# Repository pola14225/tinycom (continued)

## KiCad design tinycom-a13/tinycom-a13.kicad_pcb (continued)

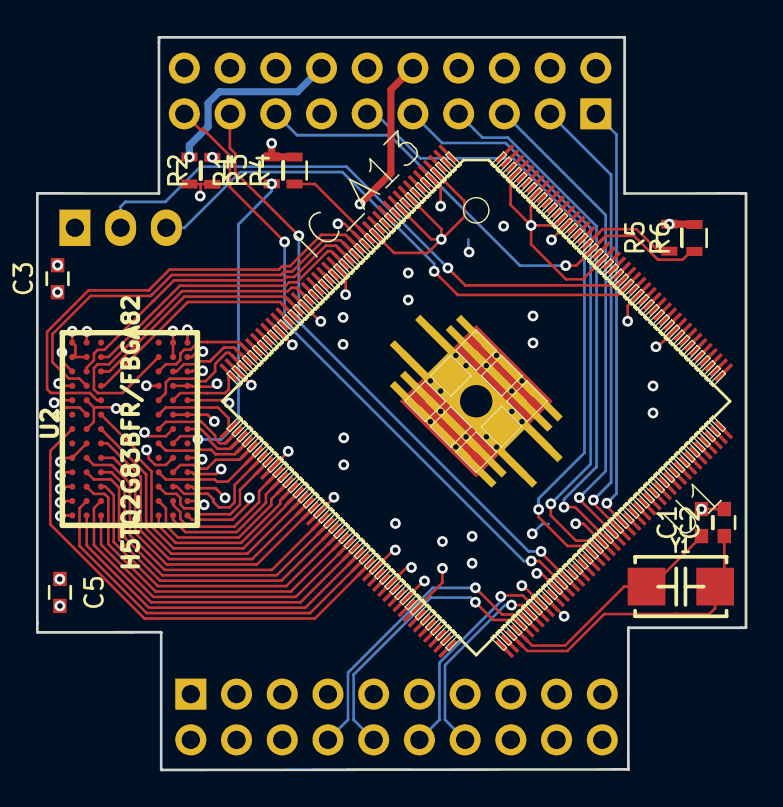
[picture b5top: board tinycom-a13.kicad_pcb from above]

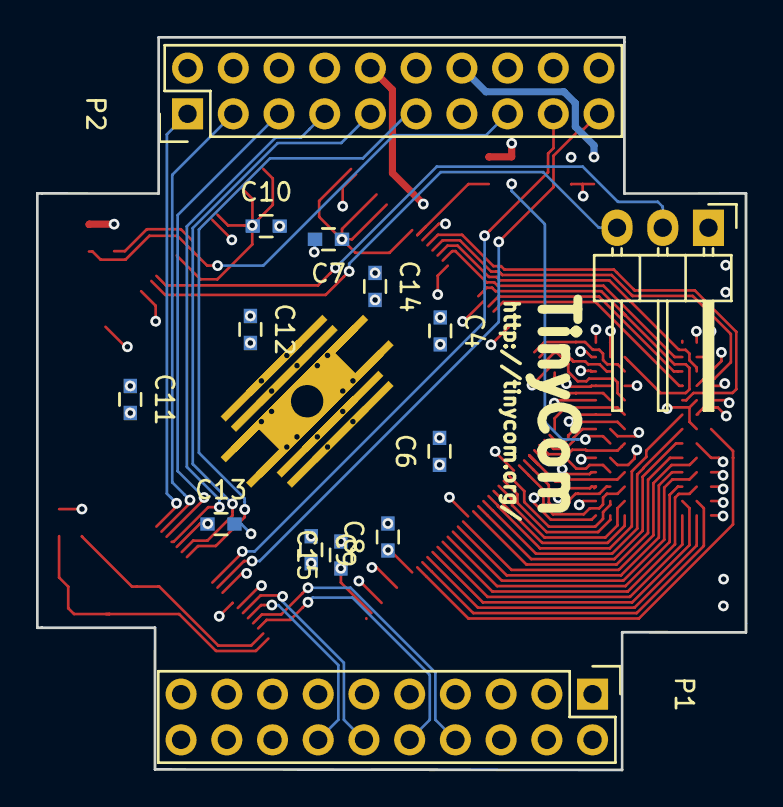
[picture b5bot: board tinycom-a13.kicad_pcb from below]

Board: 4 copper layers, 39.4 x 40.7 mm, 27 parts (14 on the bottom side), 64 nets.

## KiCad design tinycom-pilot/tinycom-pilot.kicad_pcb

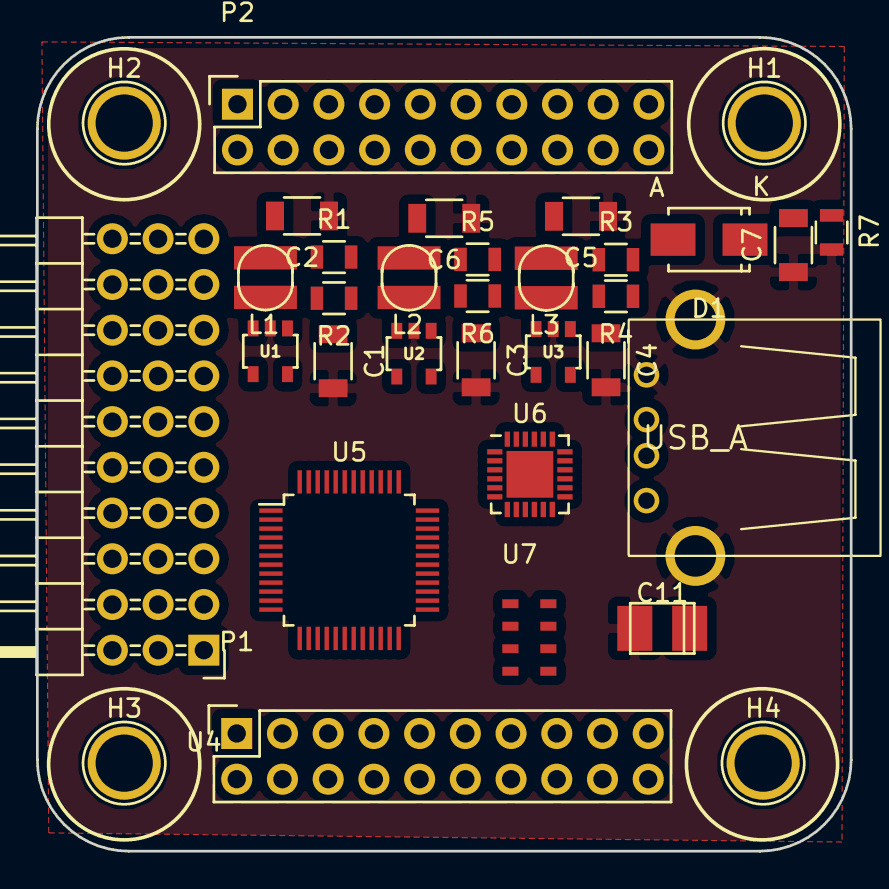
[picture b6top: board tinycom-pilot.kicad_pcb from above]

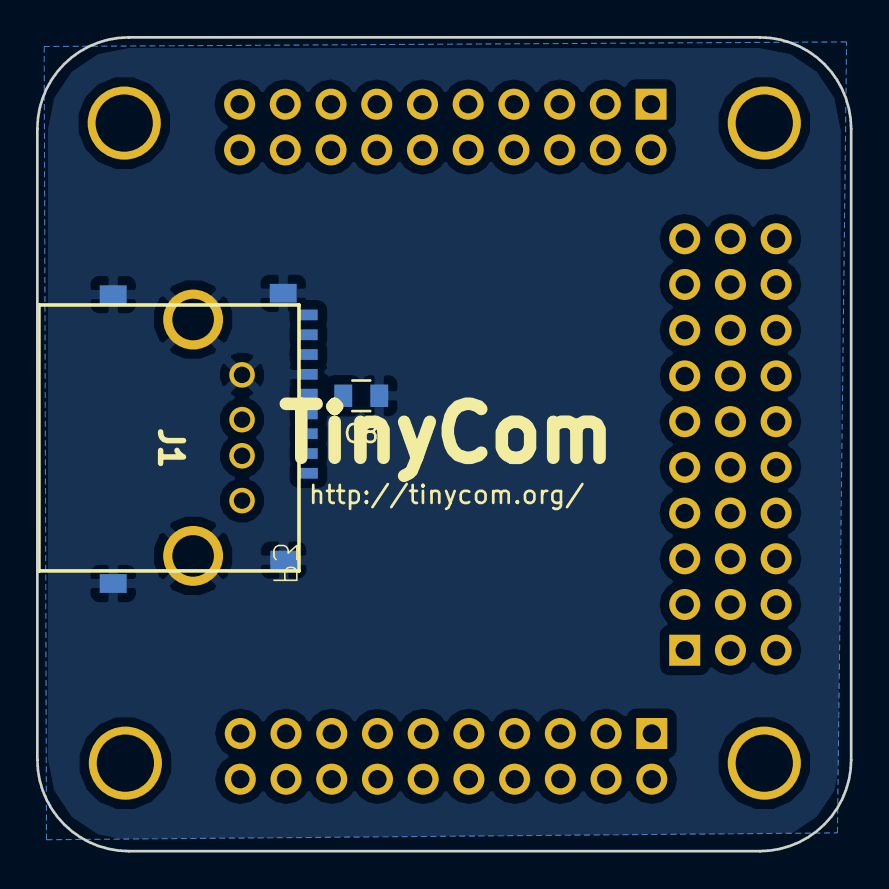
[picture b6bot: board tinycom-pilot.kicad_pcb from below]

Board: 2 copper layers, 45.2 x 45.2 mm, 35 parts (2 on the bottom side), 12 nets, no tracks yet.

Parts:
C1, C2, C3, C4, C5, C6, C7: C_Small; C_1206
C8: C_Small; C_0805
C11: CP_Small; TantalC_SizeT_EIA-3528
D1: D_Schottky_Small; SMA_Standard
H1, H2, H3, H4: 1pin
J1: MICRO_SD_HINGE; tc-MICRO_SD_HINGE_AMP
L1, L2, L3: SMD-INDUCTOR-2.2UH-20%-1.2A(0805); CD32
P1, P2: CONN_02X10; Socket_Strip_Straight_2x10
P3: USB_A; tc-con-usb-USB-A-H
R1, R2, R3, R4, R5, R6, R7: R_Small; R_0805
U1, U2, U3: SY8008BAAC; SOT23-5_Opendous
U4: conn-3x10; Pin_Header_Angled_3x10
U5: STM32-48PIN; LQFP-48_7x7mm_Pitch0.5mm
U6: MPU6050; QFN-24-1EP_4x4mm_Pitch0.5mm
U7: MS6511; ms5611

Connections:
+5V: C1.1, C3.1, C4.1, C11.1, P3.1, U1.1, U1.4, U2.1, U2.4, U3.1, U3.4
GND: C1.2, C2.1, C3.2, C4.2, C5.1, C6.1, C7.1, C8.1, C11.2, J1.6, J1.9, J1.10, J1.11, J1.12, P3.4, P3.5, R2.2, R4.2, R6.2, R7.2, U1.2, U2.2, U3.2
unnamed: L1.1, U1.3
unnamed: L2.1, U2.3
unnamed: L3.1, U3.3
unnamed: R1.2, R2.1, U1.5
unnamed: R3.2, R4.1, U3.5
unnamed: R5.2, R6.1, U2.5
VCC_14: C6.2, L2.2, R5.1
VCC_15: C5.2, L3.2, R3.1
VCC_30: C7.2, D1.1, R7.1
VCC_33: C2.2, C8.2, D1.2, J1.4, L1.2, R1.1

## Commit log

2015-10-19 first commit: start cpu module
2015-10-19 readme
2015-10-19 add img
2015-10-19 add license
2015-10-19 add missing ddr connecitons
2015-10-19 add routes
2015-10-19 full ddr route
2015-10-19 fix ddr routing
2015-10-20 before change ddr
2015-10-20 change ddr to bga78
2015-10-20 route new ddr
2015-10-20 add ddr power plane
2015-10-20 router power
2015-10-20 add missing routes in ddr
2015-10-20 add some capacitors
2015-10-20 add more capacitors
2015-10-20 image
2015-10-21 before change to 0805
2015-10-21 change to 0805 components
2015-10-21 ddr 4mil->6mil tracks, closer to cpu
2015-10-22 change other routes to 6mil
2015-10-23 add power planes
2015-10-23 adjust
2015-10-23 add pdf
2015-10-23 add png
2015-10-23 rotate
2015-10-23 fix drc
2015-10-23 svref fix
2015-10-25 add base
2015-10-25 add tinycom-drone
2015-10-25 rename
2015-10-31 prepare base
2015-10-31 adjust base
2015-11-07 ddr data routing
2015-11-08 place ground/power ddr
2015-11-08 fix power
2015-11-08 ddr3 routing
2015-11-08 before change track width
2015-11-08 add nand routes
2015-11-09 hardware license
2015-11-09 a20 schematics
2015-11-11 add capacitors
2015-11-11 add routing
2015-11-11 before autoroute
2015-11-12 add 2nd ddr
2015-11-12 change track/via size settings, update ddr footprints
2015-11-12 no tracks
2015-11-12 before delete 2nd ddr3
2015-11-13 before import routes
2015-11-13 import route
2015-11-13 add power/gnd vias
2015-11-14 add power routes
2015-11-14 before autoroute remain
2015-11-14 fixes
2015-11-20 update base board
2015-11-20 route base usb+sdcard
2015-11-20 done update base board
2015-11-21 add uboot_sel test point
2015-11-21 resize ddr pads
2015-11-21 a20 resize pad 0.3mm
2015-11-22 fix vcc_dll
2015-11-22 improve clearance
2015-11-22 clearance
2015-11-23 send for production
2015-11-28 add boards
2015-11-28 pilot pic
2015-11-28 rename wifi->basse
2015-11-28 improve base board
2015-11-28 move sata
2015-11-28 update pic
2015-11-29 before change a20 connectors
2015-11-29 change connectors
2015-11-29 start route base board
2015-11-29 before base autoroute
2015-11-29 base pic
2015-11-29 update a20 schematic
2015-12-05 update to kicad4
2015-12-05 improve placement
2015-12-05 a20 layout
2015-12-05 remove a13
2015-12-05 pics
2015-12-05 before resize vias
2015-12-05 check
2015-12-06 before reroute ddr3
2015-12-06 route ddr data
2015-12-06 reroute ddr
2015-12-06 routing ddr addr
2015-12-06 routing a20
2015-12-06 route all a20
2015-12-06 a20 pass DRC
2015-12-06 add pic
2015-12-06 base pass drc
2015-12-06 datasheet
2015-12-06 move pin
2015-12-07 send production
2015-12-09 a64 start ddr route
2015-12-10 a64 ddr routing
2015-12-10 route
2015-12-10 route uart
2015-12-10 route ddr power
2015-12-26 reroute, escape bga
2015-12-27 new route ddr
2015-12-31 routing
2016-01-01 logo
2016-01-03 power
2016-01-16 base/a20 fixes
2016-01-16 change bga pad size 0.35->0.3mm
2016-01-17 solder mask clearance
2016-01-21 before test axp209
2016-01-21 test axp209
2016-01-22 remove vias under AXP209
2016-01-30 add back a13
2016-01-30 a13 update
2016-01-30 docs
2016-01-31 a12 update
2016-02-01 fix a13 drc
2016-02-02 fix a20
2016-02-04 add video
2016-02-04 a13 updte
2016-02-04 move hdmi
2016-02-04 update base
2016-02-04 vid usb
2016-02-04 sim808 sheet
2016-02-05 a64 update
2016-03-12 update base power
2016-03-26 update a20+base (connect reset)
2016-03-26 add ground fg/bg to a20
2016-03-26 a20 remove bottom components
2016-03-27 a20 drc
2016-03-27 base drc
2016-03-27 improve base
2016-03-28 update pic base
2016-03-28 update pic a20
2016-03-29 clean
2016-03-29 missing file
2016-03-29 typo
2016-04-10 improve tinycom-usb (usb connector+antenna)
2016-04-10 fix tinycom-usb exten
2016-04-11 improve tinycom-usb
2016-04-11 update pics
2016-05-02 before replace
2016-05-02 hdmi board
2016-05-02 hdmi route
2016-05-04 improve hdmi
2016-05-06 add tinycom-mic
2016-05-06 start add i2s to a20
2016-05-06 missing files
2016-05-06 update audio
2016-05-06 add mic to hdmi
2016-05-07 start add cam to a20
2016-05-08 a20 route cam,hdmi,i2s
2016-05-08 a20 power
2016-05-20 update hdmi
2016-05-20 a20: change landing pad to 0.4
2016-05-21 a20 move caps
2016-05-21 a20 pics
2016-05-21 tinycom-hdmi rev2
2016-05-21 a20: fix CSI routing
2016-05-21 improve a20
2016-05-21 a20: add caps for camera
2016-05-21 a20 improve routing
2016-06-10 a20 route improve
2016-06-15 a20: fix i2s clock
2016-06-15 datasheets
2016-06-16 fix A20 camera
